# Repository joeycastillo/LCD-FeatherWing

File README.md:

# FeatherWing with Liquid Crystal Display

<a href="https://www.adafruit.com/product/5581"><br/>

<a href="http://www.adafruit.com/products/5581"><br/>
Click here to purchase one from the Adafruit shop</a>

This repository contains design files for the LCD FeatherWing — available at both [Adafruit](http://www.adafruit.com/products/5581) and the [Oddly Specific Objects shop](https://shop.oddlyspecificobjects.com) — and the LCD FeatherWing test jig.

PLEASE NOTE: The FeatherWing schematics and PCB designs, as well as the test jig and even the LCD data sheet and artwork are all open source hardware covered by the CC-BY-SA 4.0 license. You should feel absolute freedom to remix and change them, or even make these objects on your own for any commercial or noncommercial purpose.

The only exceptions are the Oddly Specific Objects trade marks, including the Oddly Specific Objects typography and the lazer bear artwork. If you want to make these boards and sell them, feel free to do so, and to credit OSO as inspiration! I just ask that you remove the branding from the boards if you're going to sell them on your own.

Please don't steal the bear.

## OSO-WILD-A1

This folder contains KiCad schematics and board designs for revision 01 of the LCD FeatherWing. The BOM couldn't be more simple:

* 1x [BU9796AMUV-E2](https://www.digikey.com/en/products/detail/rohm-semiconductor/BU9796AMUV-E2/5253944) 48-segment LCD controller
* 1x [732-7057-6-ND](https://www.digikey.com/en/products/detail/würth-elektronik/434351045816/5209090) tactile switch
* 2x 10K resistors (0805)
* 1x 100nF capacitor (0805)

You will also need some very basic [0.1 inch breakaway header](https://www.adafruit.com/product/392), and one of the custom LCDs described in the next section:

## OSO-WILD-A2

This folder contains designs for the liquid crystal display glass, as sent to my LCD manufacturer. If you were to design your own 48-segment LCD, the dimensions, pinout and pin spacing in the datasheet document would ensure compatibility with the FeatherWing. In addition, these files should give you an idea of the kinds of information an LCD fabricator would need to realize your design.

## OSO-WILD-A3

This folder contains a KiCad board design for revision 00 of the LCD FeatherWing tester. There is no schematic or BOM for this, but it just uses some [Feather headers](https://www.adafruit.com/product/2886) at the top, some [pogo pins](https://www.adafruit.com/product/394) in the middle and one of the aforementioned LCDs at the bottom, plus some [M2.5 standoffs](https://www.adafruit.com/product/3299).

[The test procedure](https://twitter.com/josecastillo/status/1528408183030566913) is pretty straightforward: load a script onto the Feather — preferably one that exercises each segment individually — and then place the wing in the test jig. Press the reset button on the wing (which confirms that the reset button is functional) and then watch the LCD on the tester. If the expected output appears, the board passes!

If segments appear incorrectly, check for bridged pins or bad joints on the one QFN part. If nothing displays at all, check on that as well as the two resistors by the reset button.

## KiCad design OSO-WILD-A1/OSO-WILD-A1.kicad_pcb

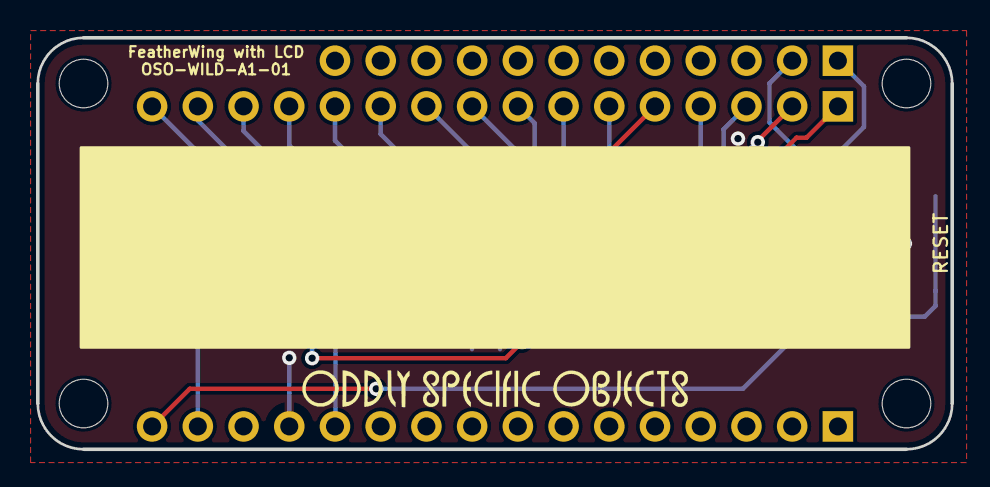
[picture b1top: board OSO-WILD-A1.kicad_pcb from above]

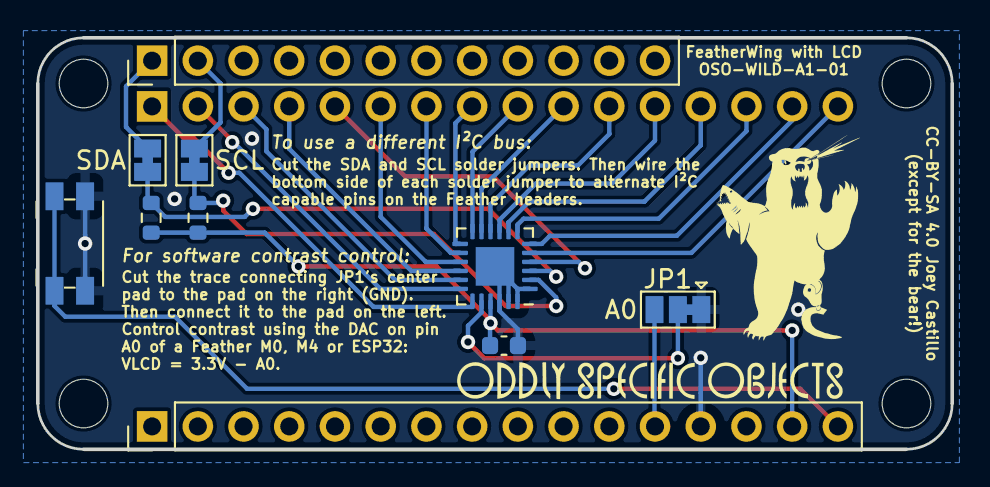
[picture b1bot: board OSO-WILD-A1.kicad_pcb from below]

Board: 2 copper layers, 50.8 x 22.9 mm, 11 parts (10 on the bottom side), 25 nets.

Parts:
C1: 0.1uF; C_0603_1608Metric
J1: feather long; PinHeader_1x16_P2.54mm_Vertical
J2: feather short; PinHeader_1x12_P2.54mm_Vertical
JP1: Jumper_3_Bridged12; SolderJumper-3_P1.3mm_Bridged12_Pad1.0x1.5mm
JP2, JP3: Jumper_2_Bridged; SolderJumper-2_P1.3mm_Bridged_Pad1.0x1.5mm
LCD1: Conn_01x16_Female; PinHeader_1x16_P2.54mm_Vertical
R1, R2: 10K; R_0603_1608Metric
SW1: SW_Push; Panasonic_EVQPUJ_EVQPUA
U1: BU9796AMUV-E2; QFN-24-1EP_4x4mm_P0.5mm_EP2.15x2.15mm

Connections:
+3V3: C1.1, J1.15, R1.1, R2.1, U1.21 (VDD)
/A0: J1.12, JP1.3 (B)
/COM0: LCD1.4, U1.16 (COM0)
/COM1: LCD1.3, U1.17 (COM1)
/COM2: LCD1.2, U1.18 (COM2)
/COM3: LCD1.1, U1.19 (COM3)
/SCL: J2.2, JP3.1 (A)
/SCL_LCD: JP3.2 (B), R2.2, U1.2 (SCL)
/SDA: J2.1, JP2.1 (A)
/SDA_LCD: JP2.2 (B), R1.2, U1.3 (SDA)
/SEG0: LCD1.5, U1.4 (SEG0)
/SEG1: LCD1.16, U1.5 (SEG1)
/SEG2: LCD1.15, U1.6 (SEG2)
/SEG3: LCD1.14, U1.7 (SEG3)
/SEG4: LCD1.13, U1.8 (SEG4)
/SEG5: LCD1.12, U1.9 (SEG5)
/SEG6: LCD1.11, U1.10 (SEG6)
/SEG7: LCD1.10, U1.11 (SEG7)
/SEG8: LCD1.9, U1.12 (SEG8)
/SEG9: LCD1.8, U1.13 (SEG9)
/SEG10: LCD1.7, U1.14 (SEG10)
/SEG11: LCD1.6, U1.15 (SEG11)
/VLCD: JP1.2 (C), U1.20 (VLCD)
/~RST: J1.16, SW1.1
GND: C1.2, J1.13, JP1.1 (A), SW1.2, U1.1 (OSCIN), U1.22 (VSS), U1.23 (TEST1), U1.24 (TEST2), U1.25 (EPAD)

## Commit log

2022-06-29 add tindie link
2022-10-12 added images
    added images and added oso logo
2022-10-12 keep photos but remove logo
2022-10-12 not available at indie at the moment

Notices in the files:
OSO-WILD-A1/OSO-WILD-A1.kicad_pcb:
CC-BY-SA 4.0 Joey Castillo
